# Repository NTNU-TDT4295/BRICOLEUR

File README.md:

# BRICOLEUR

This is the collision detection group's final submission for the course TDT4295 Computer Design Project 2018. This course aims to give students an introduction to the process of designing physical computer solutions, from start to finish. The project was completed on a budget of 10000 NOK, of which 5400 NOK were spent. 

## What is BRICOLEUR?
A bricoleur is someone who starts building something with no clear plan, adding bits here and there, cobbling together a whole while flying by the seat of their pants.

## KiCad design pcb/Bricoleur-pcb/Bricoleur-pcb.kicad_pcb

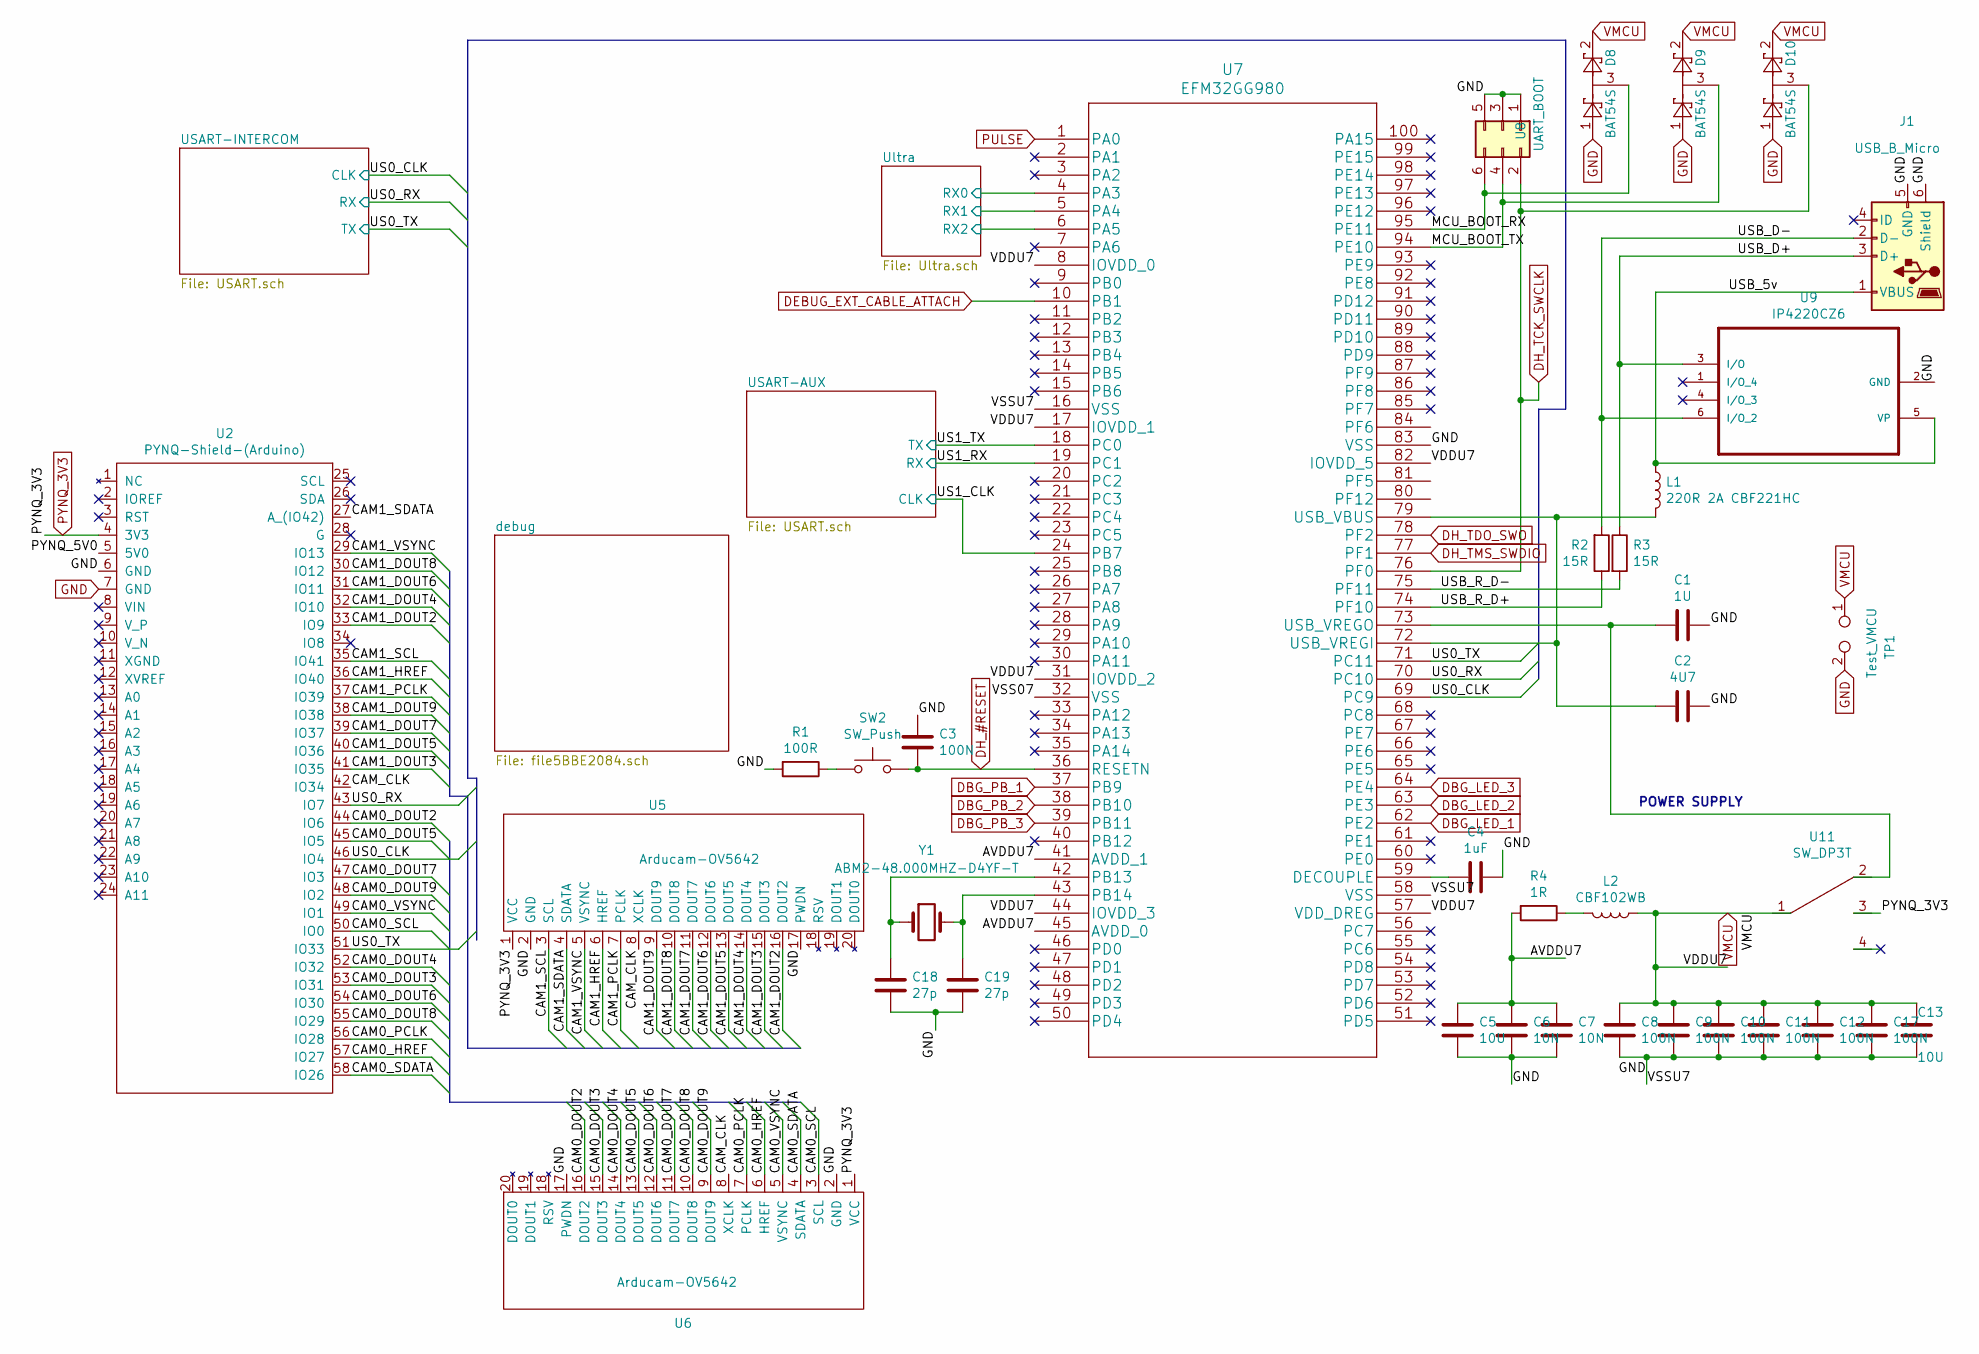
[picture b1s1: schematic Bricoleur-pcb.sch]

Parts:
C1: 1U; C_0201_0603Metric
C2: 4U7; C_0805_2012Metric
C3, C8, C9, C10, C11, C12, C17: 100N; C_0402_1005Metric
C4: 1uF; C_0603_1608Metric
C5, C13: 10U; C_0805_2012Metric
C6, C7: 10N; C_0402_1005Metric
C18, C19: 27p; C_0402_1005Metric
D8, D9, D10: BAT54S; SOT-23
J1: USB_B_Micro; USB_Micro-B_Amphenol_10103594-0001LF_Horizontal
L1: 220R 2A CBF221HC; CBF221HC
L2: CBF102WB
R1: 100R; R_0402_1005Metric
R2, R3: 15R; R_0402_1005Metric
R4: 1R; R_0402_1005Metric
SW2: SW_Push; SWITCH_WURTH_4301182043816
TP1: Test_VMCU; PinSocket_1x02_P2.54mm_Vertical
U2: PYNQ-Shield-(Arduino); PYNQ_Shield
U5, U6: Arducam-OV5642; IDC-Header_2x10_P2.54mm_Vertical
U7: EFM32GG980
U8: UART_BOOT; IDC-Header_2x03_P2.54mm_Vertical
U9: IP4220CZ6
U11: SW_DP3T; SW_CK_JS203011
Y1: ABM2-48.000MHZ-D4YF-T; XTAL

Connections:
/AVDDU7: C5.1, C6.1, C7.1, R4.2, U7.41 (AVDD_1), U7.45 (AVDD_0)
/CAM0_DOUT2: U2.44 (IO6), U6.16 (DOUT2)
/CAM0_DOUT3: U2.53 (IO31), U6.15 (DOUT3)
/CAM0_DOUT4: U2.52 (IO32), U6.14 (DOUT4)
/CAM0_DOUT5: U2.45 (IO5), U6.13 (DOUT5)
/CAM0_DOUT6: U2.54 (IO30), U6.12 (DOUT6)
/CAM0_DOUT7: U2.47 (IO3), U6.11 (DOUT7)
/CAM0_DOUT8: U2.55 (IO29), U6.10 (DOUT8)
/CAM0_DOUT9: U2.48 (IO2), U6.9 (DOUT9)
/CAM0_HREF: U2.57 (IO27), U6.6 (HREF)
/CAM0_PCLK: U2.56 (IO28), U6.7 (PCLK)
/CAM0_SCL: U2.50 (IO0), U6.3 (SCL)
/CAM0_SDATA: U2.58 (IO26), U6.4 (SDATA)
/CAM0_VSYNC: U2.49 (IO1), U6.5 (VSYNC)
/CAM1_DOUT2: U2.33 (IO9), U5.16 (DOUT2)
/CAM1_DOUT3: U2.41 (IO35), U5.15 (DOUT3)
/CAM1_DOUT4: U2.32 (IO10), U5.14 (DOUT4)
/CAM1_DOUT5: U2.40 (IO36), U5.13 (DOUT5)
/CAM1_DOUT6: U2.31 (IO11), U5.12 (DOUT6)
/CAM1_DOUT7: U2.39 (IO37), U5.11 (DOUT7)
/CAM1_DOUT8: U2.30 (IO12), U5.10 (DOUT8)
/CAM1_DOUT9: U2.38 (IO38), U5.9 (DOUT9)
/CAM1_HREF: U2.36 (IO40), U5.6 (HREF)
/CAM1_PCLK: U2.37 (IO39), U5.7 (PCLK)
/CAM1_SCL: U2.35 (IO41), U5.3 (SCL)
/CAM1_SDATA: U2.27 (A_(IO42)), U5.4 (SDATA)
/CAM1_VSYNC: U2.29 (IO13), U5.5 (VSYNC)
/CAM_CLK: U2.42 (IO34), U5.8 (XCLK), U6.8 (XCLK)
/Sheet5BB71F0E/INP: D8.3, U7.95 (PE11), U8.6
/US0_RX: U2.43 (IO7), U7.70 (PC10); also elsewhere on the board
/US1_RX: U7.19 (PC1); also elsewhere on the board
/USB_5v: J1.1 (VBUS), L1.1, U9.5 (VP)
/USB_D+: J1.3 (D+), R3.1, U9.3 (I/O)
/USB_D-: J1.2 (D-), R2.2, U9.6 (I/O_2)
/USB_R_D+: R2.1, U7.74 (PF10)
/USB_R_D-: R3.2, U7.75 (PF11)
/Ultra/RX0: U7.4 (PA3); also elsewhere on the board
/Ultra/RX1: U7.5 (PA4); also elsewhere on the board
/Ultra/RX2: U7.6 (PA5); also elsewhere on the board
/sheet5BB7B6EA/INP: D9.3, U7.94 (PE10), U8.4
DBG_LED_1: U7.62 (PE2); also elsewhere on the board
DBG_LED_2: U7.63 (PE3); also elsewhere on the board
DBG_LED_3: U7.64 (PE4); also elsewhere on the board
DBG_PB_1: U7.37 (PB9); also elsewhere on the board
DBG_PB_2: U7.38 (PB10); also elsewhere on the board
DBG_PB_3: U7.39 (PB11); also elsewhere on the board
DEBUG_EXT_CABLE_ATTACH: U7.10 (PB1); also elsewhere on the board
DH_#RESET: C3.2, SW2.2, U7.36 (RESETN); also elsewhere on the board
DH_TCK_SWCLK: D10.3, U7.76 (PF0), U8.2; also elsewhere on the board
DH_TDO_SWO: U7.78 (PF2); also elsewhere on the board
DH_TMS_SWDIO: U7.77 (PF1); also elsewhere on the board
GND: C1.1, C2.1, C3.1, C4.1, C5.2, C6.2, C7.2, C8.2, C9.2, C10.2, C11.2, C12.2, C13.2, C17.2, C18.2, C19.2, D8.1, D9.1, D10.1, J1.5 (GND), J1.6 (Shield), R1.2, TP1.2, U2.6 (GND), U2.7 (GND), U5.2 (GND), U5.17 (PWDN), U6.2 (GND), U6.17 (PWDN), U7.16 (VSS), U7.58 (VSS), U7.83 (VSS), U8.1, U8.3, U8.5, U9.2 (GND); also elsewhere on the board
unnamed: C1.2, U7.73 (USB_VREGO), U11.2
unnamed: C2.2, L1.2, U7.72 (USB_VREGI), U7.79 (USB_VBUS)
unnamed: C4.2, U7.59 (DECOUPLE)
unnamed: C18.1, U7.42 (PB13), Y1.1
unnamed: C19.1, U7.43 (PB14), Y1.2
unnamed: L2.2, R4.1
unnamed: R1.1, SW2.1
PULSE: U7.1 (PA0); also elsewhere on the board
PYNQ_3V3: U2.4 (3V3), U5.1 (VCC), U6.1 (VCC), U11.3
VMCU: C8.1, C9.1, C10.1, C11.1, C12.1, C13.1, C17.1, D8.2, D9.2, D10.2, L2.1, TP1.1, U7.8 (IOVDD_0), U7.17 (IOVDD_1), U7.31 (IOVDD_2), U7.44 (IOVDD_3), U7.57 (VDD_DREG), U7.82 (IOVDD_5), U11.1; also elsewhere on the board

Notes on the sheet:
POWER SUPPLY

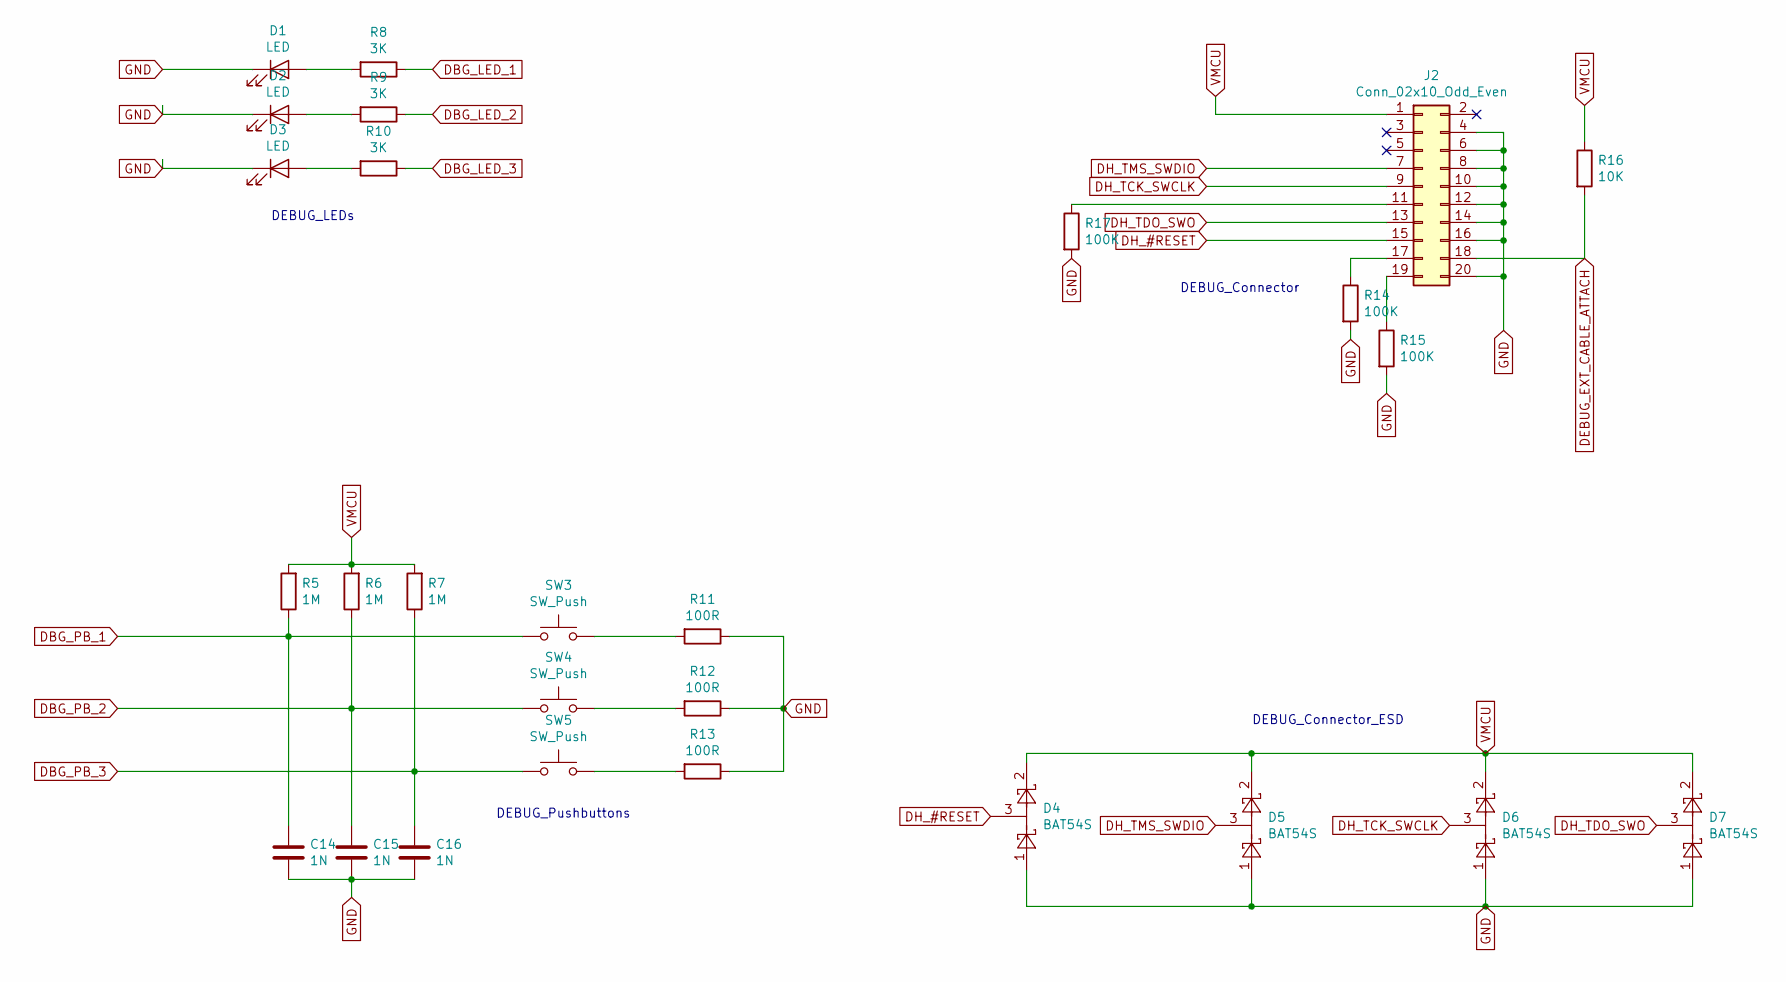
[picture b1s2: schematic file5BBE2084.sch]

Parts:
C14, C15, C16: 1N; C_0402_1005Metric
D1, D2, D3: LED; LED_0201_0603Metric
D4, D5, D6, D7: BAT54S; SOT-23
J2: Conn_02x10_Odd_Even; IDC-Header_2x10_P2.54mm_Vertical
R5, R6, R7: 1M; R_0402_1005Metric
R8: 3K; R_0402_1005Metric
R9, R10: 3K; C_0402_1005Metric
R11, R12, R13: 100R; R_0402_1005Metric
R14, R15, R17: 100K; R_0402_1005Metric
R16: 10K; R_0402_1005Metric
SW3, SW4, SW5: SW_Push; SWITCH_WURTH_4301182043816

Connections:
DBG_LED_1: R8.1; also elsewhere on the board
DBG_LED_2: R9.1; also elsewhere on the board
DBG_LED_3: R10.1; also elsewhere on the board
DBG_PB_1: C14.1, R5.1, SW3.1; also elsewhere on the board
DBG_PB_2: C15.1, R6.1, SW4.1; also elsewhere on the board
DBG_PB_3: C16.1, R7.1, SW5.1; also elsewhere on the board
DEBUG_EXT_CABLE_ATTACH: J2.18, R16.2; also elsewhere on the board
DH_#RESET: D4.3, J2.15; also elsewhere on the board
DH_TCK_SWCLK: D6.3, J2.9; also elsewhere on the board
DH_TDO_SWO: D7.3, J2.13; also elsewhere on the board
DH_TMS_SWDIO: D5.3, J2.7; also elsewhere on the board
GND: C14.2, C15.2, C16.2, D1.1 (K), D2.1 (K), D3.1 (K), D4.1, D5.1, D6.1, D7.1, J2.4, J2.6, J2.8, J2.10, J2.12, J2.14, J2.16, J2.20, R11.1, R12.1, R13.1, R14.2, R15.2, R17.2; also elsewhere on the board
unnamed: D1.2 (A), R8.2
unnamed: D2.2 (A), R9.2
unnamed: D3.2 (A), R10.2
unnamed: J2.11, R17.1
unnamed: J2.17, R14.1
unnamed: J2.19, R15.1
unnamed: R11.2, SW3.2
unnamed: R12.2, SW4.2
unnamed: R13.2, SW5.2
VMCU: D4.2, D5.2, D6.2, D7.2, J2.1, R5.2, R6.2, R7.2, R16.1; also elsewhere on the board

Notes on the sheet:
DEBUG_LEDs
DEBUG_Pushbuttons
DEBUG_Connector
DEBUG_Connector_ESD

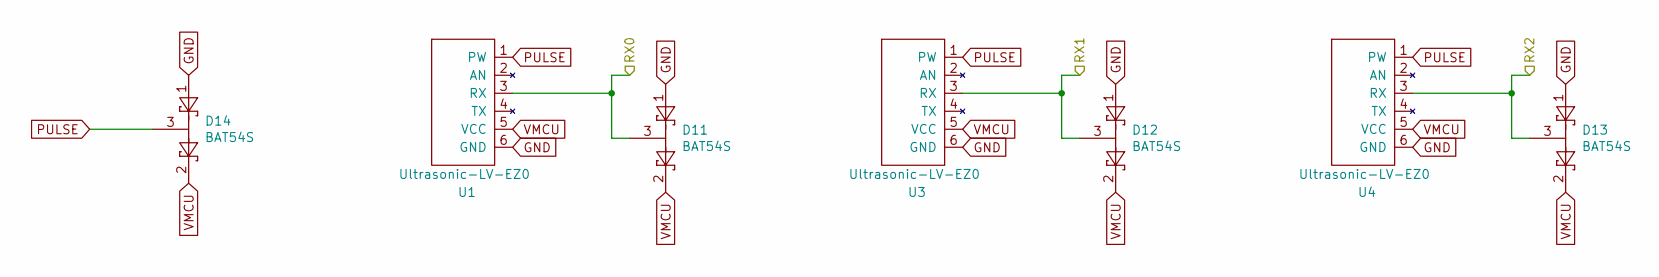
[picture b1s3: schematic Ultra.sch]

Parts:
D11, D12, D13, D14: BAT54S; SOT-23
U1, U3, U4: Ultrasonic-LV-EZ0; IDC-Header_2x03_P2.54mm_Vertical

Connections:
/Ultra/RX0: D11.3, U1.3 (RX); also elsewhere on the board
/Ultra/RX1: D12.3, U3.3 (RX); also elsewhere on the board
/Ultra/RX2: D13.3, U4.3 (RX); also elsewhere on the board
GND: D11.1, D12.1, D13.1, D14.1, U1.6 (GND), U3.6 (GND), U4.6 (GND); also elsewhere on the board
PULSE: D14.3, U1.1 (PW), U3.1 (PW), U4.1 (PW); also elsewhere on the board
VMCU: D11.2, D12.2, D13.2, D14.2, U1.5 (VCC), U3.5 (VCC), U4.5 (VCC); also elsewhere on the board

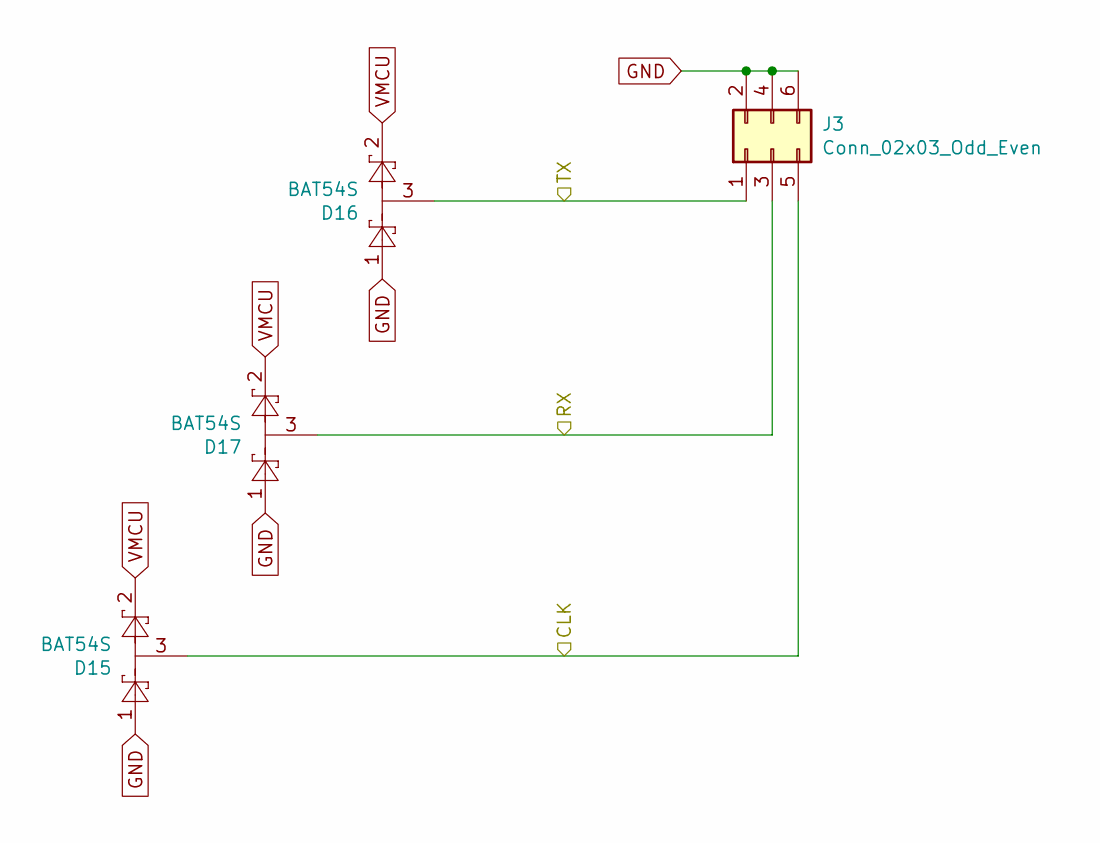
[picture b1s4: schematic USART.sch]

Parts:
D17, D18, D19: BAT54S; SOT-23
J3: Conn_02x03_Odd_Even; IDC-Header_2x03_P2.54mm_Vertical

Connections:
/US0_RX: D17.3, J3.3; also elsewhere on the board
GND: D17.1, D18.1, D19.1, J3.2, J3.4, J3.6; also elsewhere on the board
VMCU: D17.2, D18.2, D19.2; also elsewhere on the board

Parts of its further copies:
D15, D16, D20: BAT54S; SOT-23
J4: Conn_02x03_Odd_Even; IDC-Header_2x03_P2.54mm_Vertical

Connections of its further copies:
/US1_RX: D20.3, J4.3; also elsewhere on the board
GND: D15.1, D16.1, D20.1, J4.2, J4.4, J4.6; also elsewhere on the board
VMCU: D15.2, D16.2, D20.2; also elsewhere on the board

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
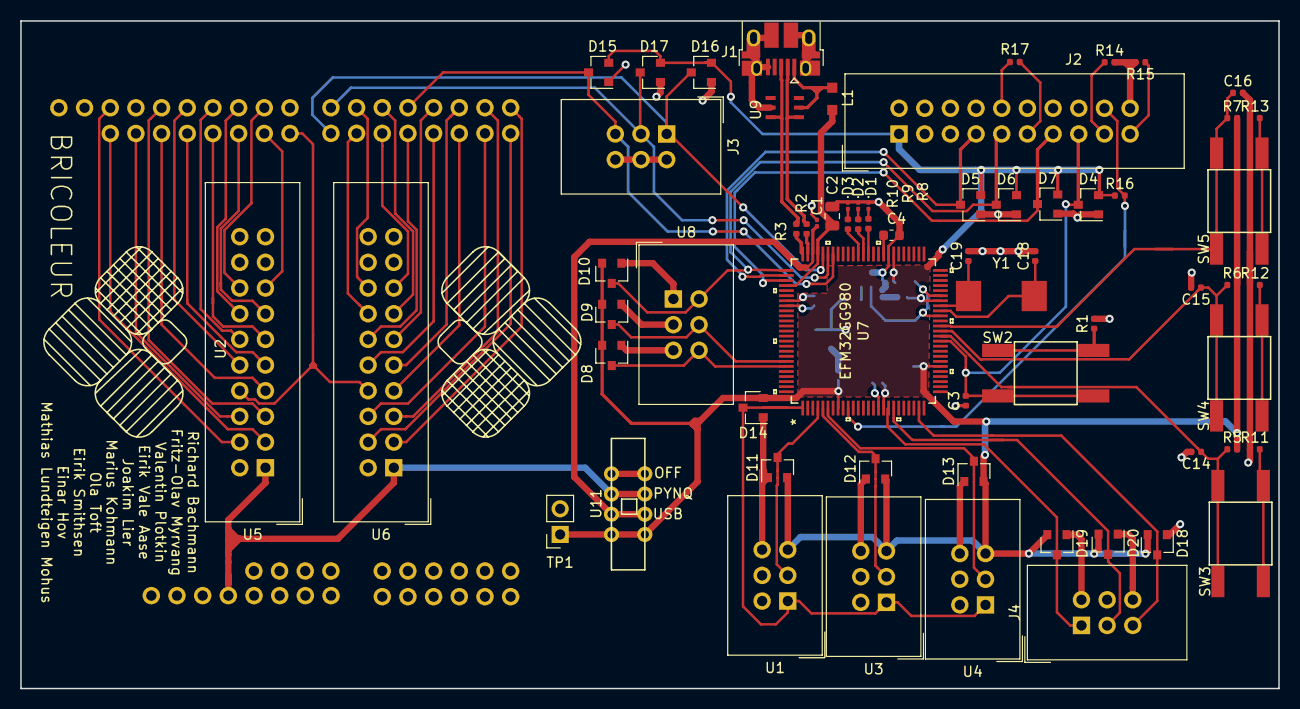
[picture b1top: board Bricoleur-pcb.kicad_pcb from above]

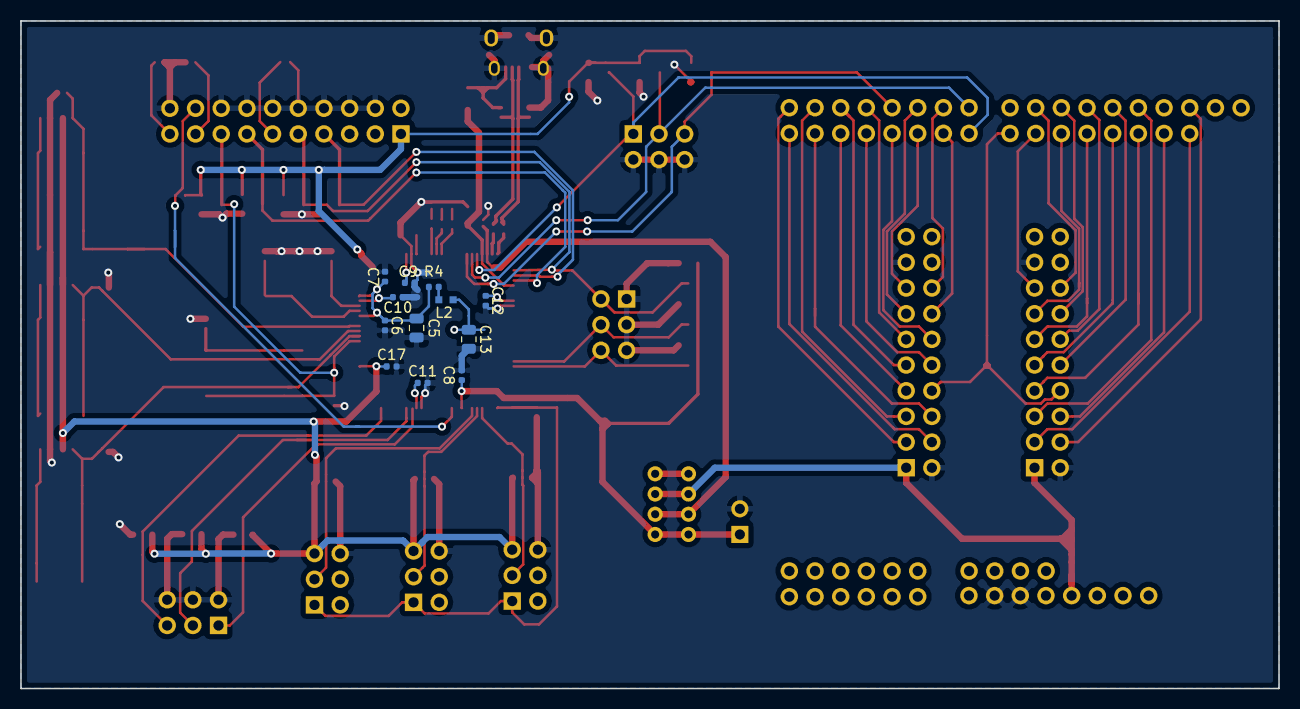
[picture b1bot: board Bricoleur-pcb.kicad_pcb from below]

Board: 2 copper layers, 124.5 x 66.0 mm, 78 parts (12 on the bottom side), 75 nets.

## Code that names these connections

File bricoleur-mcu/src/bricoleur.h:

/*******************************************************************************
 * Project and custom hardware specific definitions
 ******************************************************************************/
// PCB: L2 er 220nH i stedet for 1000

// On-board LEDs
#define DBG_LED_PORT gpioPortE
#define DBG_LED_1 2
#define DBG_LED_2 3
#define DBG_LED_3 4

// Push buttons
#define DBG_PB_PORT gpioPortB
#define DBG_PB_1 9
#define DBG_PB_2 10
#define DBG_PB_3 11

// Ultrasonic sensors
#define ULTRA_PORT gpioPortA
#define ULTRA_PULSE 0
#define ULTRA_RX0 3
#define ULTRA_RX1 4 
#define ULTRA_RX2 5
#define ULTRA_NUM 2  // Number of sensors in use

// USART-AUX - feeds status to external entity
// NOTE: There are two different ports, sorry
#define USART_AUX_PORT_1 gpioPortC  // For TX and RX
#define USART_AUX_PORT_2 gpioPortB  // For CLK
#define USART_AUX_TX 0
#define USART_AUX_RX 1
#define USART_AUX_CLK 7
#define USART_AUX_CS 8  // Unused
#define USART_AUX_LOC USART_ROUTE_LOCATION_LOC0
#define USART_AUX_PORTNUM 0

// USART-FPGA - data transfer to and from PYNQ
#define USART_FPGA_PORT gpioPortC
#define USART_FPGA_TX 11
#define USART_FPGA_RX 10
#define USART_FPGA_CLK 9
#define USART_FPGA_CS 8
#define USART_FPGA_LOC USART_ROUTE_LOCATION_LOC2 
#define USART_FPGA_PORTNUM 0

// USB - Not really used, but here for the sake of completion
#define USB_PORT gpioPortF
#define USB_R_Dn 11
#define USB_R_Dp 10


typedef struct usart_buffer_t {
    unsigned int head;
    unsigned int tail;
    unsigned int length;
    unsigned int maxLength;
    bool wrapped;
    char data[64];  // Treat as byte array
} USART_Buffer;

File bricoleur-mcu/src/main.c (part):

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
    /* Pin numbers:
     * Name             MCU    EXP
     * USART1_TX	PC0
     * USART1_RX	PC1
     * USART1_CLK	PB7
     * USART1_CS	PB8    (UNUSED)
     */

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  
    /* Pin numbers:
     * Name             MCU    EXP
     * USART1_TX	PC11
     * USART1_RX	PC10
     * USART1_CLK	PC9
     * USART1_CS	PC8    (UNUSED)
     */

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
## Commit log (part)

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2018-09-18 PCB first commit
2018-09-18 Microcontroller power supply candidate
2018-09-19 Power supply done, debug interface started
2018-09-20 Ultrasonic: Get 3D position of object from distances from sensors
2018-09-21 Legger til 'algoritme' for bildebehandling og produksjon av dybdekart
2018-09-21 Add object detection and tracking demo
2018-09-21 Ultrasonic: Compile and flash to ARM EFM32
2018-09-21 updated gitignore
2018-09-25 Ultrasonic: Add flow from input via position to line
2018-09-25 Cleanup: Ultrasonic: Update .gitignore
2018-09-25 Ultrasonic: Check if object will collide with our system
2018-09-25 Schematics and footprints almost done
2018-09-26 Use sequence of images, check if approaching or not
2018-09-26 Upload rosetta files with sample programs
    Check https://github.com/maltanar/rosetta for instructions on what you
    need to compile this, get it over to the PYNQ and run the programs.
2018-09-27 added new set of test images, with static camera. Updated algorithm to improve stability
2018-09-27 Convert to circular buffer. Also, flips logic into correct form in isMoving
2018-09-27 Fixed.
2018-09-27 Start of layout work + minor tweaks
2018-09-28 Fix paths to images, show time in ms
2018-09-28 Add sensor interfacing
    Code for the HC-SR04 ultrasonic sensor is included.
2018-09-28 Ultrasonic: Fix and simplify circular buffer
2018-09-28 More ESD protection, USART output, more footprints
2018-09-28 Time different functions, clean up code
2018-09-30 Narrowed down component placement, continued routing
2018-09-30 Power and clock networks ready (probably).
2018-09-30 Routing sonars and AUX-UART
2018-09-30 Moar routing
2018-10-01 Some routing tweaks
2018-10-01 Overwrite
2018-10-01 Layout finished.
2018-10-03 Header rotated - ethernet connector is too big.
2018-10-03 Added support for multiple heuristics
2018-10-03 Pcb finished???
2018-10-03 Ultrasonic: Get real input from one sensor to analysis system
2018-10-03 Small fix.
2018-10-03 Moar fixes.
2018-10-03 Ultrasonic: Added header files
    Added header files for main and sensor.
    Put in prototypes and structs, but not #defines
2018-10-03 Use emlib typedef for GPIO port
2018-10-03 Set all trigger pins as output
2018-10-08 Add basic USART functionality
    Sends distances over UART.
    Also writes sensor 0 and 1 readings to LCD.
2018-10-09 Initial commit, draft of the gauss module, is 100% no chance of being correct, needs more work
2018-10-09 Removed python_packages, shouldnt be there
2018-10-10 Add support for EZ0 rangefinder
    Adds support for LV-MaxSonar-EZ0 rangefinder
    and removes support for HC-SR04.
2018-10-10 Added module tester
2018-10-12 More comments
2018-10-12 More edits, commented gaussian kernel in, needs to be expanded with floating/fixedpoint calculations
2018-10-12 Add gitignore
2018-10-15 Add README for ultrasonic
2018-10-15 Ultrasonic: Get correct position and improve output
    Fix a bug which caused the position to be incremented for each iteration instead of being reset.
    Write a lot more output to miniterm, and make it easier to add more.
    Increase baud rate for faster output.
2018-10-15 Add empty project for MCU
    Empty Simplicity Studio v4 project which links against emlib.
2018-10-15 started looking at fixed point arithmetics
2018-10-15 Add spidev to our SPI controller
    This is an unrecommended "buggy" way to activate spidev on the device.
    Do we care enough to do it properly?
2018-10-16 Integrate SBT project
2018-10-16 Ignore test run dir
2018-10-16 Just use zero values to pass test and fix compilation issues
2018-10-16 is this gaussian blur working? I see decimal points.
2018-10-17 Ultrasonic testdata: Run with static, collected testdata from file
2018-10-17 added some todos, minor formatting
2018-10-17 Grayscaling works
2018-10-18 Restructure code
2018-10-18 Fix tests for FIFO queue
2018-10-19 Use new sensor setup procedure
    This procedure follows the startup described in
    the sensors' datasheet.
2018-10-19 Ultrasonic testdata: isMoving() checks if change in distance is larger than error margin
2018-10-19 First example code USART slave/master
2018-10-19 Flush buffer if no movement
2018-10-20 Implement dummy data generator
2018-10-22 Add axi compliant dummy data generator
2018-10-22 Added main to GaussianBlur to enable compiling to .v
2018-10-22 tready is input signal, not output
2018-10-23 Added a simple Inverter module, with a test. Added a main to compile all modules down to verilog with a bash script, see compile.sh and main.scala
2018-10-23 Fixed bugs in grayscale module, updated tests and added a new test
2018-10-24 Ultrasonic testdata: Check if what we see is an object, or if it's the wall
2018-10-24 Added support for testing grayscale with an entire image
2018-10-24 Forgot a }
2018-10-24 Added test image
2018-10-24 Scala doesn't like creating directories, make sure one exist for tests to run
2018-10-24 Ultrasonic testdata: Increase treshold while calibrating wall distance after a certain time
    If the sensors are balancing between two different distances, we might have to wait a long time for 3 equal distances in a row (or never get 3 equal distances).
    Therefore, increase the treshold to accept distances that are close, but not exactly equal, after a certain time
2018-10-24 recompile
2018-10-24 Read serial ouput from EZ0
    This will use the serial output from the EZ0 instead of
    the pulse output.
    The distance is output in whole inches, so the code
    has been refactored to handle this.
    This removes much of the noise we have seen in the distance
    readings, as the noise were introduced when we were reading the pulses.
2018-10-24 the start of the main module. Work in progress
2018-10-26 Ultrasonic: Better handling of real data
    Manual merge from Ultrasonic testdata.
    Flush buffer when detecting wall.
    Detect if an object is not the wall.
2018-10-26 Make Grayscale AXI compliant
2018-10-26 Change from cm to inches
    #MURICA.
    Also, we don't need to typecast so much and can use unsigned int instead of float.
2018-10-26 Order functions by when they are called
    Because I was tired of remembering/guessing where a function was.
2018-10-26 Use memset() to reset totalString
    Don't have to use totalStringLength to constantly keep track of how many characters are in the string right now.
2018-10-26 Ultrasonic: Remove 3D
    3D was not yet used, and I don't think we will use it. Check the git history if you need to add it later.
    Remove 3D function.
    Remove 2D part of 2D functions to simplify.
2018-10-26 Ultrasonic: Replace buildString() by strcat()
2018-10-29 Fixed an error with asserting the tkeep signal, ~0.U becomes 1,~(0.U(4.W)) becomes 1111
2018-10-29 MCU basic protocol draft
2018-10-29 Use separate U(S)ART for debug and sensor input
2018-10-29 Make Dilation AXI compliant
2018-10-29 Fix tests
2018-10-29 Assert ready to GB so it outputs something
2018-10-30 Now DDGA outputs fixpoint numbers, as it probably should be
2018-10-30 Fix failing DDGA tests
2018-10-31 Added a general purpose GaussianBlur, any kernelsize
2018-10-31 Added testing for general purpose Gaussian Blur
2018-10-31 generated some bigger hardcoded test sets
2018-10-31 clock signal was gone. Now it is back. Hallelujah 🥳
2018-10-31 Only do something when tready has been asserted
2018-10-31 Added counter logic for valid output, and correct edge values
2018-10-31 Updated testing for bigger range
2018-10-31 Updated grayscale testing
2018-11-01 Ignore a bunch of files
2018-11-01 Input should have been output
2018-11-02 Ignore files
2018-11-02 small fix to some test 🕋
2018-11-02 WE DID IT BOYS GAUSSIAN BLUR IS A GO 🎉🎉🎉
2018-11-02 main to build correct sized modules
2018-11-04 PCB specific .h file and further work on mcu mvp
2018-11-05 After some testing in vivado, it seems the gaussian blur now is in sync with both greyscale and the DMA
2018-11-06 FIFO, Grayscale and Gauss now works very nice, in vivado as well
2018-11-06 Added the notebook used for testing, is nice to have this available on git
2018-11-06 Made Dilation similar to Gaussian Blur, it compiles
2018-11-07 Use correct kernel values
2018-11-07 Remove unused includes
2018-11-07 Remove LCD code
    Prepare for moving to PCB
2018-11-07 Ultrasonic_to_mcu: Create helper file ultrasonic.c
    main() in main.c can willCollideUltrasonic() in ultrasonic.c
    ultrasonic.c will handle the rest
2018-11-07 Find max of kernel values
2018-11-07 Cleanup dilation. commit number 100 🎉
2018-11-07 Move all to mcu folder
2018-11-07 Put stuff in folder to make it mergable with master
2018-11-08 added framebuffer for smoothing, tweaked settings and began a new heuristic
2018-11-08 adding closestpos heuristic dunno if working
2018-11-09 fixed colors on the rectangles, re-added framebuffer for less spasmic results
2018-11-09 Add fixedpoint 32 to uint8 converter
2018-11-09 More tweaking of magic numbers, tests may have been gutted to test for these numbers, forgive me
2018-11-11 Ignore generated folder
2018-11-11 Fix whitespace
2018-11-11 Move some files, start on UART component
2018-11-12 remove completed TODOs from code
2018-11-12 added datawidth and binary point to grayscale module
2018-11-12 tinkering away. Started the composite heuristic which will hopefully rock this world
2018-11-12 Add some converters from uint8 to fixedpoint 32
2018-11-12 Add more tests to converters
2018-11-13 Camera stuff
2018-11-14 mcu: Get a conclusion of the chance of collision from ultrasonic
    Ultrasonic will give a conclusion of the chance of collision as a value between 0 and 1.
    The mcu will then map this local conclusion to a global conclusion which can be used by the imponator.
2018-11-14 Fix USART setup
    Use correct location for USART-AUX and configure it as UART.
    Configure correct USART for USART-FPGA.
2018-11-14 Refactor to use common constant
2018-11-14 Use define constants
2018-11-14 Threshold, absdiff (non-working), FIFOAlt with uint)
2018-11-14 Set start adress for linker in Simplicity Studio
    This is needed when flashing to an MCU with a bootloader as the program
    will be placed after the bootloader in memory.
2018-11-15 added a small feature to further reduce noise. Also redone some formatting
2018-11-15 Absdiff is working
2018-11-16 Cleanup, labeling, schematic size reduction
2018-11-16 Try implementing absdiff and threshold
2018-11-16 Create downscaler component
2018-11-17 added printing in binary so we can send it to the mcu
2018-11-17 added call to writetogpio and the respective byte value
2018-11-17 Absdiff works (dont cause crash)
2018-11-17 Disable sleep-waiting for data
    Use busy wait for incoming sensor data.
    The sleep approach might have caused some problems, so removing
    it to have one less thing that can go wrong.
2018-11-18 Add a module to convert packed grayscale bytes to 32-bit grayscale values
2018-11-18 fix bugs with multiple overlays and make video run forever
2018-11-18 fix bug with wrong pin was used
2018-11-18 Remove unused buffers
    We won't send data to the PYNQ and we will only send single bytes
    on AUX.
2018-11-18 Absdiff has been declared BUG FREE
2018-11-18 Small improvements
2018-11-19 another go at fixing the readme
2018-11-19 refacotring
2018-11-19 mcu: Fix map function
2018-11-19 Implement treadyIn signal in absdiff
2018-11-19 Small edits to Dilate, getting ready for integration
2018-11-19 Remove unused register, poke validIn in test
2018-11-19 Ultrasonic: Fix division-by-zero bug when object is not moving or moving slowly
2018-11-19 Ultrasonic: Make sure buffer->length can get longer than 1
2018-11-19 Ultrasonic: Fix logic bug
    If isMovingPosition is false, we should not flush the buffer.
    isMovingPositions will return false when buffer.length == 0, and this will lead to the buffer never getting longer than 1.
2018-11-20 Final Vivado project files
2018-11-20 User manual first draft 🎉🎉 🕋
2018-11-20 Ultrasonic: Fix output
    Use max value until we see the wall
    Fix a bug where we would get nan
    Combine conclusions from camera and ultrasonic.

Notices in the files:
bricoleur-mcu/src/main.c:
<b>(C) Copyright 2014 Silicon Labs, http://www.silabs.com</b>
This file is licensed under the Silicon Labs Software License Agreement. See
"http://developer.silabs.com/legal/version/v11/Silicon_Labs_Software_License_Agreement.txt"
parts and their libraries:
Copyright 2016 Accelerated Designs. All rights reserved.
